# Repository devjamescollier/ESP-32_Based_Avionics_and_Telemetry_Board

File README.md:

# ESP32-Based Avionics & Telemetry Board

2S Li-Po flight computer built around an ESP32-WROOM-32E module. Fuses two IMUs, a magnetometer, and a barometer, logs flight data to microSD, and drives four servos and one ESC from a fused, reverse-polarity-protected battery input with a switched servo rail.

Designed for small fixed-wing aircraft with USB programming, multiple test points, and battery-voltage monitoring.

## Table of Contents
- [Schematic](#schematic)
- [Layout](#layout)
- [3D Model](#3d-model)
- [Overview](#overview)
- [Specifications](#specifications)
- [Results](#results)
- [Software](#software)
- [Tech Stack](#tech-stack)
- [Equipment](#equipment)
- [Manufacturing](#manufacturing)
- [Repository Structure](#repository-structure)
- [Contact](#contact)
- [License](#license)

## Schematic

## Layout

## 3D Model

## Overview

The board is a compact 4-layer flight computer centred on an ESP32-WROOM-32E module.

| Section                         | Description                                                                                                            |
| ---                             | ---                                                                                                                    |
| **Digital Core**                | The ESP32-WROOM-32E runs sensor fusion, logging, and actuator control, programmed through a CP2102N USB-UART bridge.   |
| **Sensors**                     | LSM6DSV32X and ASM330LHH IMUs on SPI, plus an LIS3MDL magnetometer and MS5611 barometer on I²C.                        |
| **Actuator Outputs**            | Four servo headers and one ESC header, each with a 1 kΩ series resistor and 100 kΩ pull-down to stay low through reset. |
| **User Interface**              | EN and BOOT buttons, three status LEDs, an active buzzer, and a microSD socket for data logging.                       |
| **Power**                       | An XT30 input feeds a 15 A fuse, P-FET reverse-battery protection, a switched servo rail, and an AP63203 3.3 V buck regulator. |

## Specifications

| Parameter                         | Value                                  |
| --------------------------------- | -------------------------------------- |
| **Microcontroller**               | ESP32-WROOM-32E-N4                     |
| **IMUs**                          | LSM6DSV32X and ASM330LHH, SPI          |
| **Magnetometer**                  | LIS3MDL, I²C                           |
| **Barometer**                     | MS5611-01BA03, I²C                     |
| **Storage**                       | microSD, SPI                           |
| **Outputs**                       | 4 servo + 1 ESC                        |
| **Power Input**                   | 2S Li-Po, 6.0–8.4 V                    |
| **Idle Current**                  | 48 mA (battery), 62 mA (USB)           |
| **Servo Rail Rating**             | 6 A continuous (calculated)            |
| **Regulation**                    | 3.301 V, 8.4 mVpp ripple               |
| **Board mass**                    | 18.4 g                                 |
| **Board size**                    | 80 mm × 50 mm                          |

## Results

PCB measurements from the JLCPCB-assembled prototype:

| Measurement           | Expected        | Measured          | Notes                            |
| --------------------: | --------------: | ----------------: | -------------------------------: |
| **VBAT**              | 7.4–8.4 V       | 8.21 V            | 2S Li-Po at ~80 % charge         |
| **SERVO_PWR**         | ≈ VBAT          | 8.19 V            | Q4 drop ≈ 20 mV                  |
| **REG_IN**            | Supply − Vf     | 7.92 V / 4.78 V   | From servo rail / USB            |
| **+3.3 V**            | 3.30 V ± 2 %    | 3.301 V           | 8.4 mVpp ripple at 1.1 MHz       |
| **V_SENSE**           | 2.30 V          | 2.31 V            | Battery-voltage ADC divider      |
| **Soft start**        | ~1 ms           | 1.1 ms            | Servo-rail switch-on             |
| **Reverse polarity**  | No conduction   | 0 mA              | −8.2 V on J7 for 5 s, no damage  |
| **IMU accel (Z)**     | +1.000 g        | +0.998 / +0.997 g | LSM6DSV32X / ASM330LHH, flat     |
| **IMU gyro**          | ~0 °/s          | < ±0.18 °/s       | Both IMUs, static                |
| **Magnetic field**    | Geomagnetic     | 28.5 / −1.2 / 41.0 µT | LIS3MDL, flat, north-aligned |
| **Pressure**          | ~1013 hPa       | 1013.2 hPa        | MS5611, 23.6 °C                  |
| **Soak temperature**  | No brown-out    | 41.2 °C           | ESP32 after 30 min, buck 38.7 °C |

USB programming, sensor IDs, I²C, microSD (SPI), and clean PWM edges (< 40 ns) on all outputs were verified using a digital multimeter, oscilloscope, bench power supply, and thermometer. Servo-rail load testing at 6 A, vibration, and EMI testing are still to be performed.

## Software

The diagnostic firmware targets the ESP32-WROOM-32E and is written in C with ESP-IDF.

### Programming

1. Install ESP-IDF (tested with v6.1-beta1).
2. Open [`Software/fc_diag`](Software/fc_diag) and run `idf.py set-target esp32`.
3. Build the firmware with `idf.py build`.
4. Connect the board over USB; the auto-program circuit enters the bootloader automatically.
5. Flash and monitor the firmware with `idf.py -p PORT flash monitor`.

## Tech Stack

| PCB Design | Firmware Development | Version Control | Repository Hosting | Language |
| :--------: | :------------------: | :-------------: | :----------------: | :------: |
|  |  |  |  |  |

## Equipment

| Tool                   | Model | Purpose                                              |
| ---------------------- | ----- | ---------------------------------------------------- |
| **Oscilloscope**       | —     | Soft-start, ripple, and PWM edge measurements        |
| **Multimeter**         | —     | Rail voltages, continuity, and current draw          |
| **Bench power supply** | —     | Current-limited power-up and reverse-polarity test   |
| **Thermometer**        | —     | Component temperatures during the soak test          |
| **Loupe (10×)**        | —     | Solder-joint and assembly inspection                 |
| **Soldering station**  | —     | Hand assembly of the through-hole components         |

## Manufacturing

Production files are provided in the [`Manufacturing`](Manufacturing/) directory:

- [`ESP-32_Based_Avionics_Telemetry_Board_Gerbers.zip`](Manufacturing/ESP-32_Based_Avionics_Telemetry_Board_Gerbers.zip) — Gerber and drill archive, ready to upload
- [`BOM.csv`](Manufacturing/Assembly/BOM.csv) — Bill of materials with LCSC part numbers (SMT parts)
- [`positions.csv`](Manufacturing/Assembly/positions.csv) — Component placement data (CPL)
- [`Hand_Assembly_THT.csv`](Manufacturing/Assembly/Hand_Assembly_THT.csv) — Through-hole parts to hand-solder
- [`CPL_rotation_review.csv`](Manufacturing/Assembly/CPL_rotation_review.csv) — Polarized parts to check in JLCPCB's placement preview
- [`Gerbers`](Manufacturing/Gerbers/) — Copper, mask, silkscreen, paste, outline, and drill files

### Ordering from JLCPCB

1. Upload the Gerber zip. Set **Layers: 4**, **Thickness: 1.6 mm**, **Stackup: JLC04161H-7628**, **Surface finish: ENIG**. Leave everything else at the default.
2. Enable **PCB Assembly**, top side only, and upload `BOM.csv` and `positions.csv`.
3. In the placement preview, check each part in `CPL_rotation_review.csv`, especially the diodes, LEDs, electrolytic capacitors, MOSFETs and ICs. Fix any rotations before confirming.
4. Hand-solder the through-hole parts in `Hand_Assembly_THT.csv` (buzzer, servo and ESC headers, XT30, slide switch). Their LCSC numbers are listed so they can be ordered from LCSC in the same order.

All 37 LCSC part numbers were in stock in the JLCPCB parts snapshot checked on 2026-11-09. Re-confirm live stock at checkout.

### Notes

- The servo rail (pin 2 of J2–J5) carries the battery voltage directly, up to 8.4 V. Use high-voltage (HV) servos rated for 2S.
- The ESC header's centre pin (J8 pin 2) is not connected, so the ESC's BEC cannot back-feed the board.

Design and manufacturing checks (ERC, DRC, BOM/CPL reconciliation, Gerber checks) are recorded in [`Docs/Verification`](Docs/Verification/VERIFICATION.md).

## Repository Structure

```text
ESP-32_Based_Avionics_and_Telemetry_Board
├── Docs                                                                           Contains board related images and verification records
│   ├── Images                                                                     Contains images of the board render, board layout, and board schematic
│   │   ├── ESP-32_Based_Avionics_Telemetry_Board_3D_Model.png                     3D model in PNG format
│   │   ├── ESP-32_Based_Avionics_Telemetry_Board_Layout.png                       Layout in PNG format
│   │   ├── ESP-32_Based_Avionics_Telemetry_Board_Schematic.png                    Schematic in PNG format
│   │   └── ESP-32_Based_Avionics_Telemetry_Board_Schematic.pdf                    Schematic in PDF format
│   └── Verification                                                               Contains ERC, DRC, BOM, and Gerber check records
│       ├── BOM_CPL_Check.json                                                     BOM and placement reconciliation
│       ├── DRC.rpt                                                                DRC report
│       ├── ERC.rpt                                                                ERC report
│       ├── Gerber_Check.txt                                                       Gerber and drill check
│       └── VERIFICATION.md                                                        Design-check summary
├── Hardware                                                                       Contains all KiCad PCB files
│   └── KiCad_Files                                                                Contains 3D models for board render, footprints for layout, KiCad project files, and symbols for schematic.
│       ├── 3D_Models                                                              Contains STEP files for the 3D render of the board
│       │   ├── Buzzer_12x9.5RM7.6.step                                            STEP for buzzer
│       │   ├── C_0603_1608Metric.step                                             STEP for 0603 capacitors
│       │   ├── C_0805_2012Metric.step                                             STEP for 0805 capacitors
│       │   ├── CP_Elec_6.3x5.4.step                                               STEP for electrolytic capacitors
│       │   ├── D_SMA.step                                                         STEP for SS54 diodes
│       │   ├── D_SOD-323.step                                                     STEP for B5819WS diode
│       │   ├── ESP32-WROOM-32E.step                                               STEP for ESP32-WROOM-32E module
│       │   ├── L_Changjiang_FNR4030S.step                                         STEP for buck inductor
│       │   ├── LED_0603_1608Metric.step                                           STEP for LEDs
│       │   ├── LGA-12_2x2mm_P0.5mm.step                                           STEP for LIS3MDL magnetometer
│       │   ├── LGA-14_3x2.5mm_P0.5mm_LayoutBorder3x4y.step                        STEP for IMUs
│       │   ├── Littelfuse_0451.step                                               STEP for 15 A fuse
│       │   ├── microSD_HC_Hirose_DM3AT-SF-PEJM5.step                              STEP for microSD socket
│       │   ├── Molex_105017-0001.step                                             STEP for USB Micro-B receptacle
│       │   ├── PinHeader_1x03_P2.54mm_Vertical.step                               STEP for servo and ESC headers
│       │   ├── QFN-28-1EP_5x5mm_P0.5mm_EP3.35x3.35mm.step                         STEP for CP2102N
│       │   ├── R_0603_1608Metric.step                                             STEP for 0603 resistors
│       │   ├── SOIC-8_3.9x4.9mm_P1.27mm.step                                      STEP for AO4407A MOSFETs
│       │   ├── SOT-23-6.step                                                      STEP for USBLC6-2SC6
│       │   ├── SOT-23.step                                                        STEP for MMBT3904 transistors
│       │   ├── SS12D10G5.step                                                     STEP for slide switch
│       │   ├── TS-1187A-B-A-B.step                                                STEP for tactile switches
│       │   ├── TSOT-23-6.step                                                     STEP for AP63203 buck regulator
│       │   └── XT30PW-M.step                                                      STEP for XT30 battery connector
│       ├── Footprints                                                             Contains footprints for PCB components
│       │   └── Avionics_Footprints.pretty                                         Contains custom board footprints
│       │       ├── ESP32-WROOM-32E_Espressif.kicad_mod
│       │       ├── SW_Slide_SPDT_Vertical_ShouHan_SS12D10_P4.8mm.kicad_mod
│       │       ├── TE_MS5611-01BA03_LGA-8_3x5mm_P1.25mm.kicad_mod
│       │       └── USB_Micro-B_Molex-105017-0001_EdgeSilk.kicad_mod
│       ├── ESP-32_Based_Avionics_Telemetry_Board.kicad_pcb                        KiCad PCB file
│       ├── ESP-32_Based_Avionics_Telemetry_Board.kicad_pro                        KiCad project file
│       ├── ESP-32_Based_Avionics_Telemetry_Board.kicad_sch                        KiCad Schematic file
│       ├── fp-lib-table
│       ├── sym-lib-table
│       └── Symbols                                                                Contains schematic symbols for PCB schematic
│           └── FC_Fixed.kicad_sym                                                 ESP32, CP2102N, sensor, and MS5611 symbols
├── LICENSE                                                                        CERN Open Hardware Licence Version 2 - Permissive for hardware
├── Manufacturing                                                                  Contains bill of materials, pick-and-place, and Gerber files.
│   ├── Assembly                                                                   Contains bill of materials and pick-and-place
│   │   ├── BOM.csv                                                                Bill of materials
│   │   ├── CPL_rotation_review.csv                                                Polarized parts placement review
│   │   ├── Hand_Assembly_THT.csv                                                  Through-hole parts for hand soldering
│   │   └── positions.csv                                                          Pick-and-place
│   ├── Gerbers                                                                    Contains Gerber files
│   │   ├── ESP-32_Based_Avionics_Telemetry_Board-B_Cu.gbl
│   │   ├── ESP-32_Based_Avionics_Telemetry_Board-B_Mask.gbs
│   │   ├── ESP-32_Based_Avionics_Telemetry_Board-B_Paste.gbp
│   │   ├── ESP-32_Based_Avionics_Telemetry_Board-B_Silkscreen.gbo
│   │   ├── ESP-32_Based_Avionics_Telemetry_Board-Edge_Cuts.gm1
│   │   ├── ESP-32_Based_Avionics_Telemetry_Board-F_Cu.gtl
│   │   ├── ESP-32_Based_Avionics_Telemetry_Board-F_Mask.gts
│   │   ├── ESP-32_Based_Avionics_Telemetry_Board-F_Paste.gtp
│   │   ├── ESP-32_Based_Avionics_Telemetry_Board-F_Silkscreen.gto
│   │   ├── ESP-32_Based_Avionics_Telemetry_Board-GND.g1
│   │   ├── ESP-32_Based_Avionics_Telemetry_Board-job.gbrjob
│   │   ├── ESP-32_Based_Avionics_Telemetry_Board-NPTH-drl_map.gbr
│   │   ├── ESP-32_Based_Avionics_Telemetry_Board-NPTH.drl
│   │   ├── ESP-32_Based_Avionics_Telemetry_Board-PTH-drl_map.gbr
│   │   ├── ESP-32_Based_Avionics_Telemetry_Board-PTH.drl
│   │   └── ESP-32_Based_Avionics_Telemetry_Board-PWR.g2
│   └── ESP-32_Based_Avionics_Telemetry_Board_Gerbers.zip                          Gerber archive for JLCPCB upload
├── Software                                                                       Contains C firmware and software license
│   ├── LICENSE                                                                    MIT License for firmware
│   └── fc_diag                                                                    ESP-IDF diagnostic firmware project
│       ├── CMakeLists.txt
│       ├── sdkconfig.defaults
│       └── main
│           ├── CMakeLists.txt
│           └── fc_diag.c                                                          Firmware for ESP32
└── README.md                                                                      Project README
```

## Contact
- GitHub: [@devjamescollier](https://github.com/devjamescollier)
- Email: [jwcollie@usc.edu](mailto:jwcollie@usc.edu)

## License

Copyright © 2026 James Collier

The hardware design files are licensed under the CERN Open Hardware
Licence Version 2 – Permissive. See [LICENSE](LICENSE).

The firmware is licensed under the MIT License. See
[Software/LICENSE](Software/LICENSE).

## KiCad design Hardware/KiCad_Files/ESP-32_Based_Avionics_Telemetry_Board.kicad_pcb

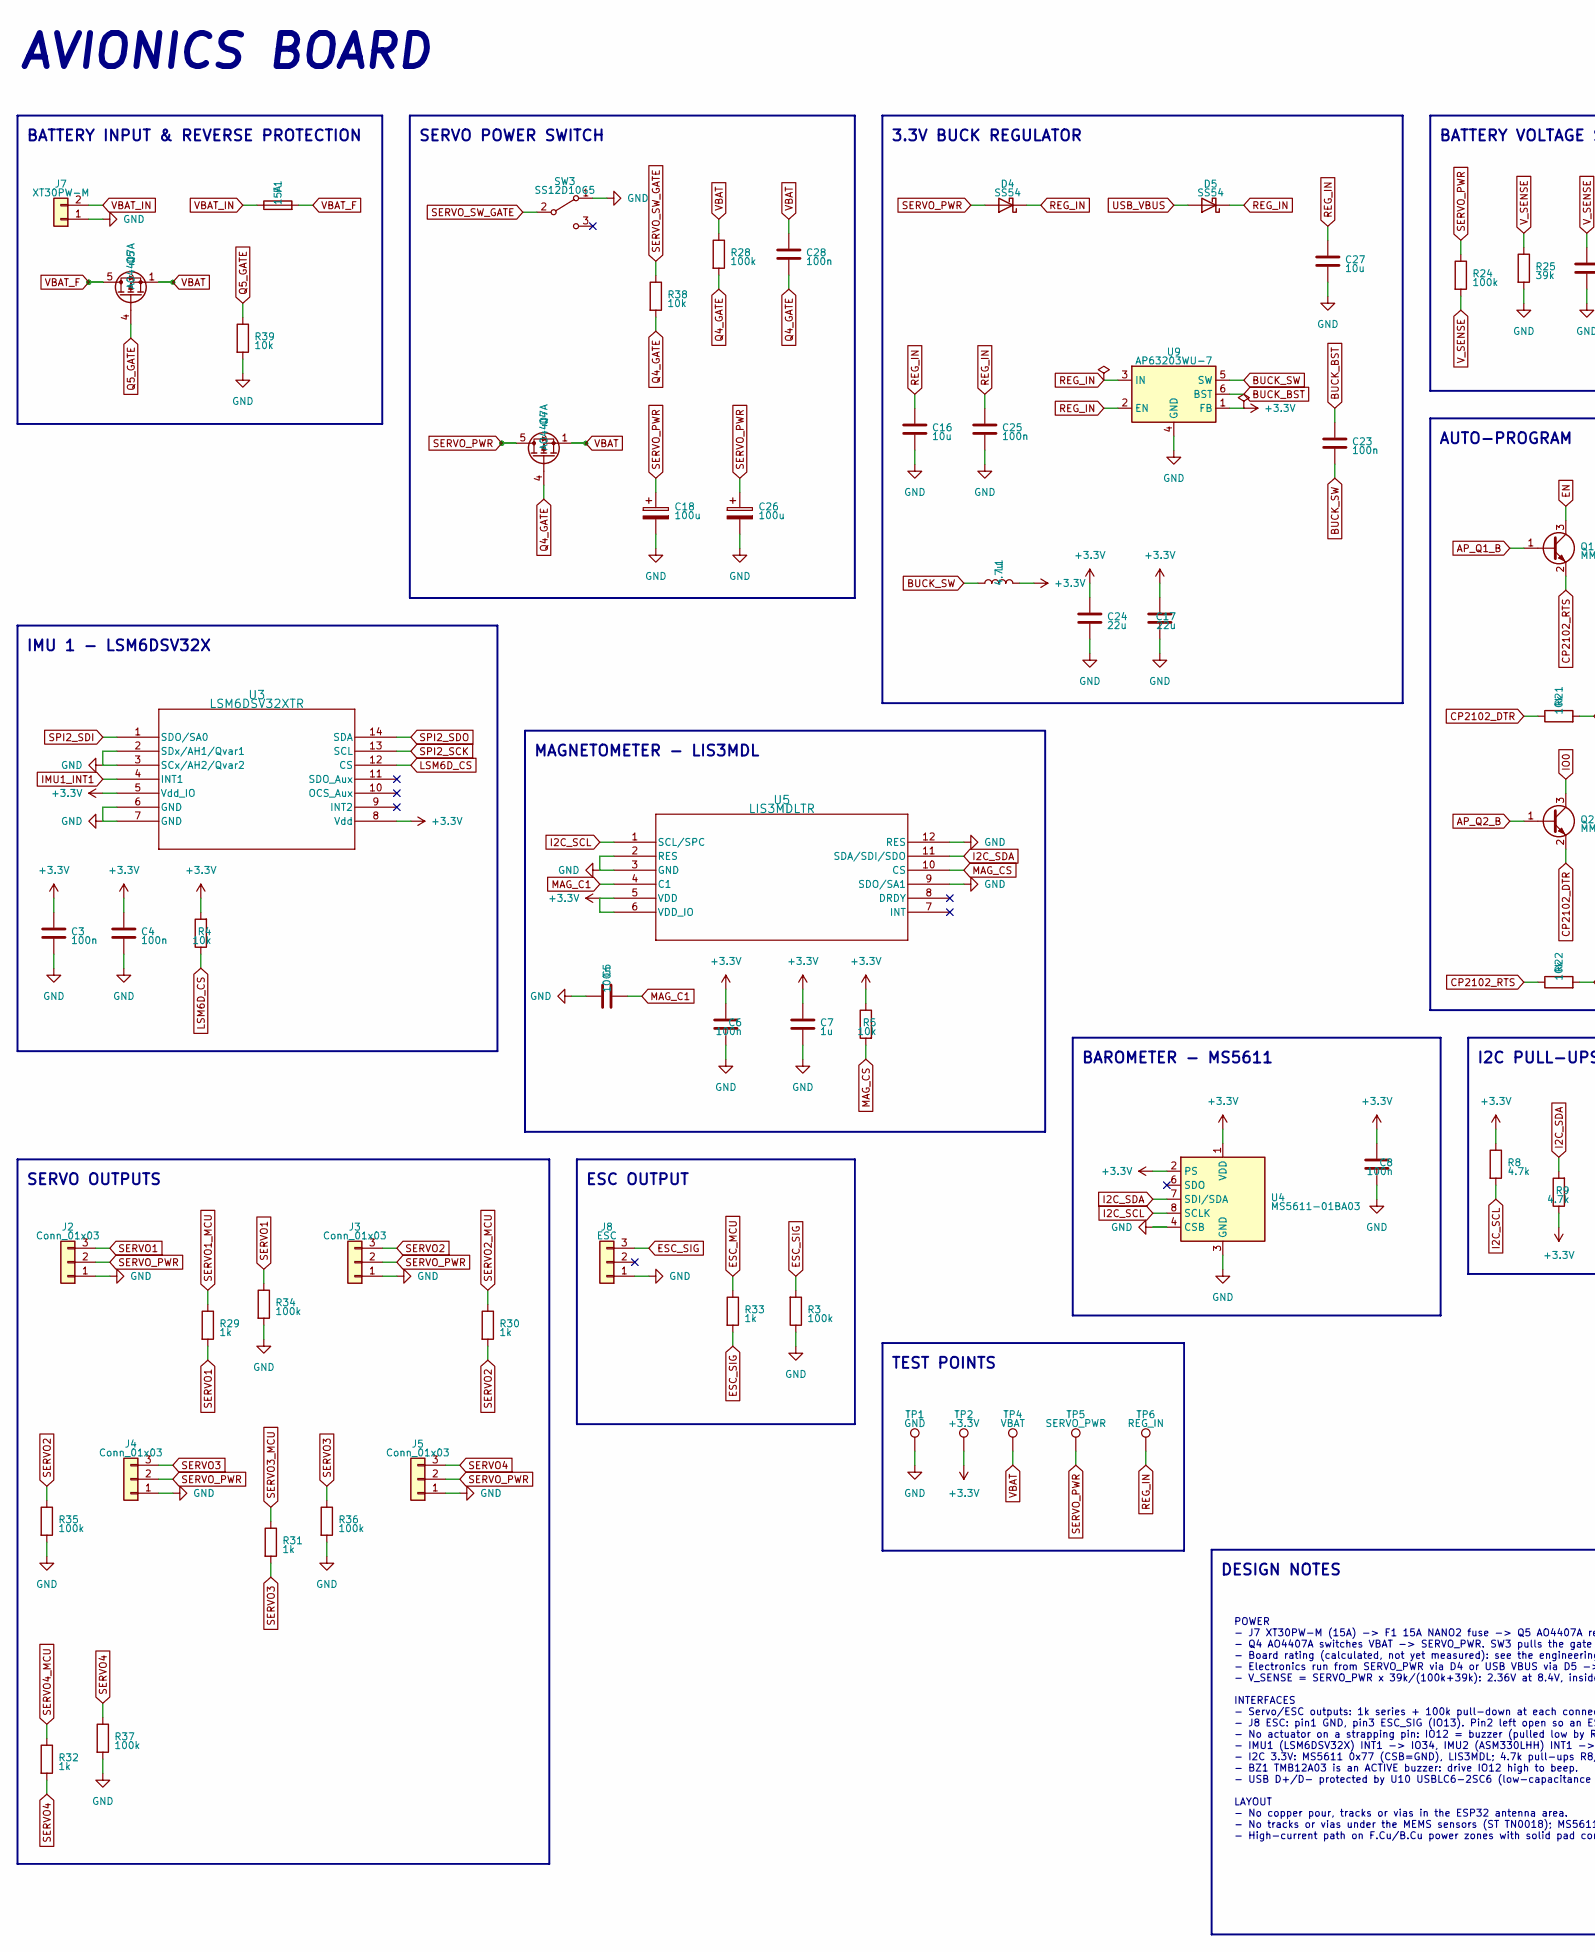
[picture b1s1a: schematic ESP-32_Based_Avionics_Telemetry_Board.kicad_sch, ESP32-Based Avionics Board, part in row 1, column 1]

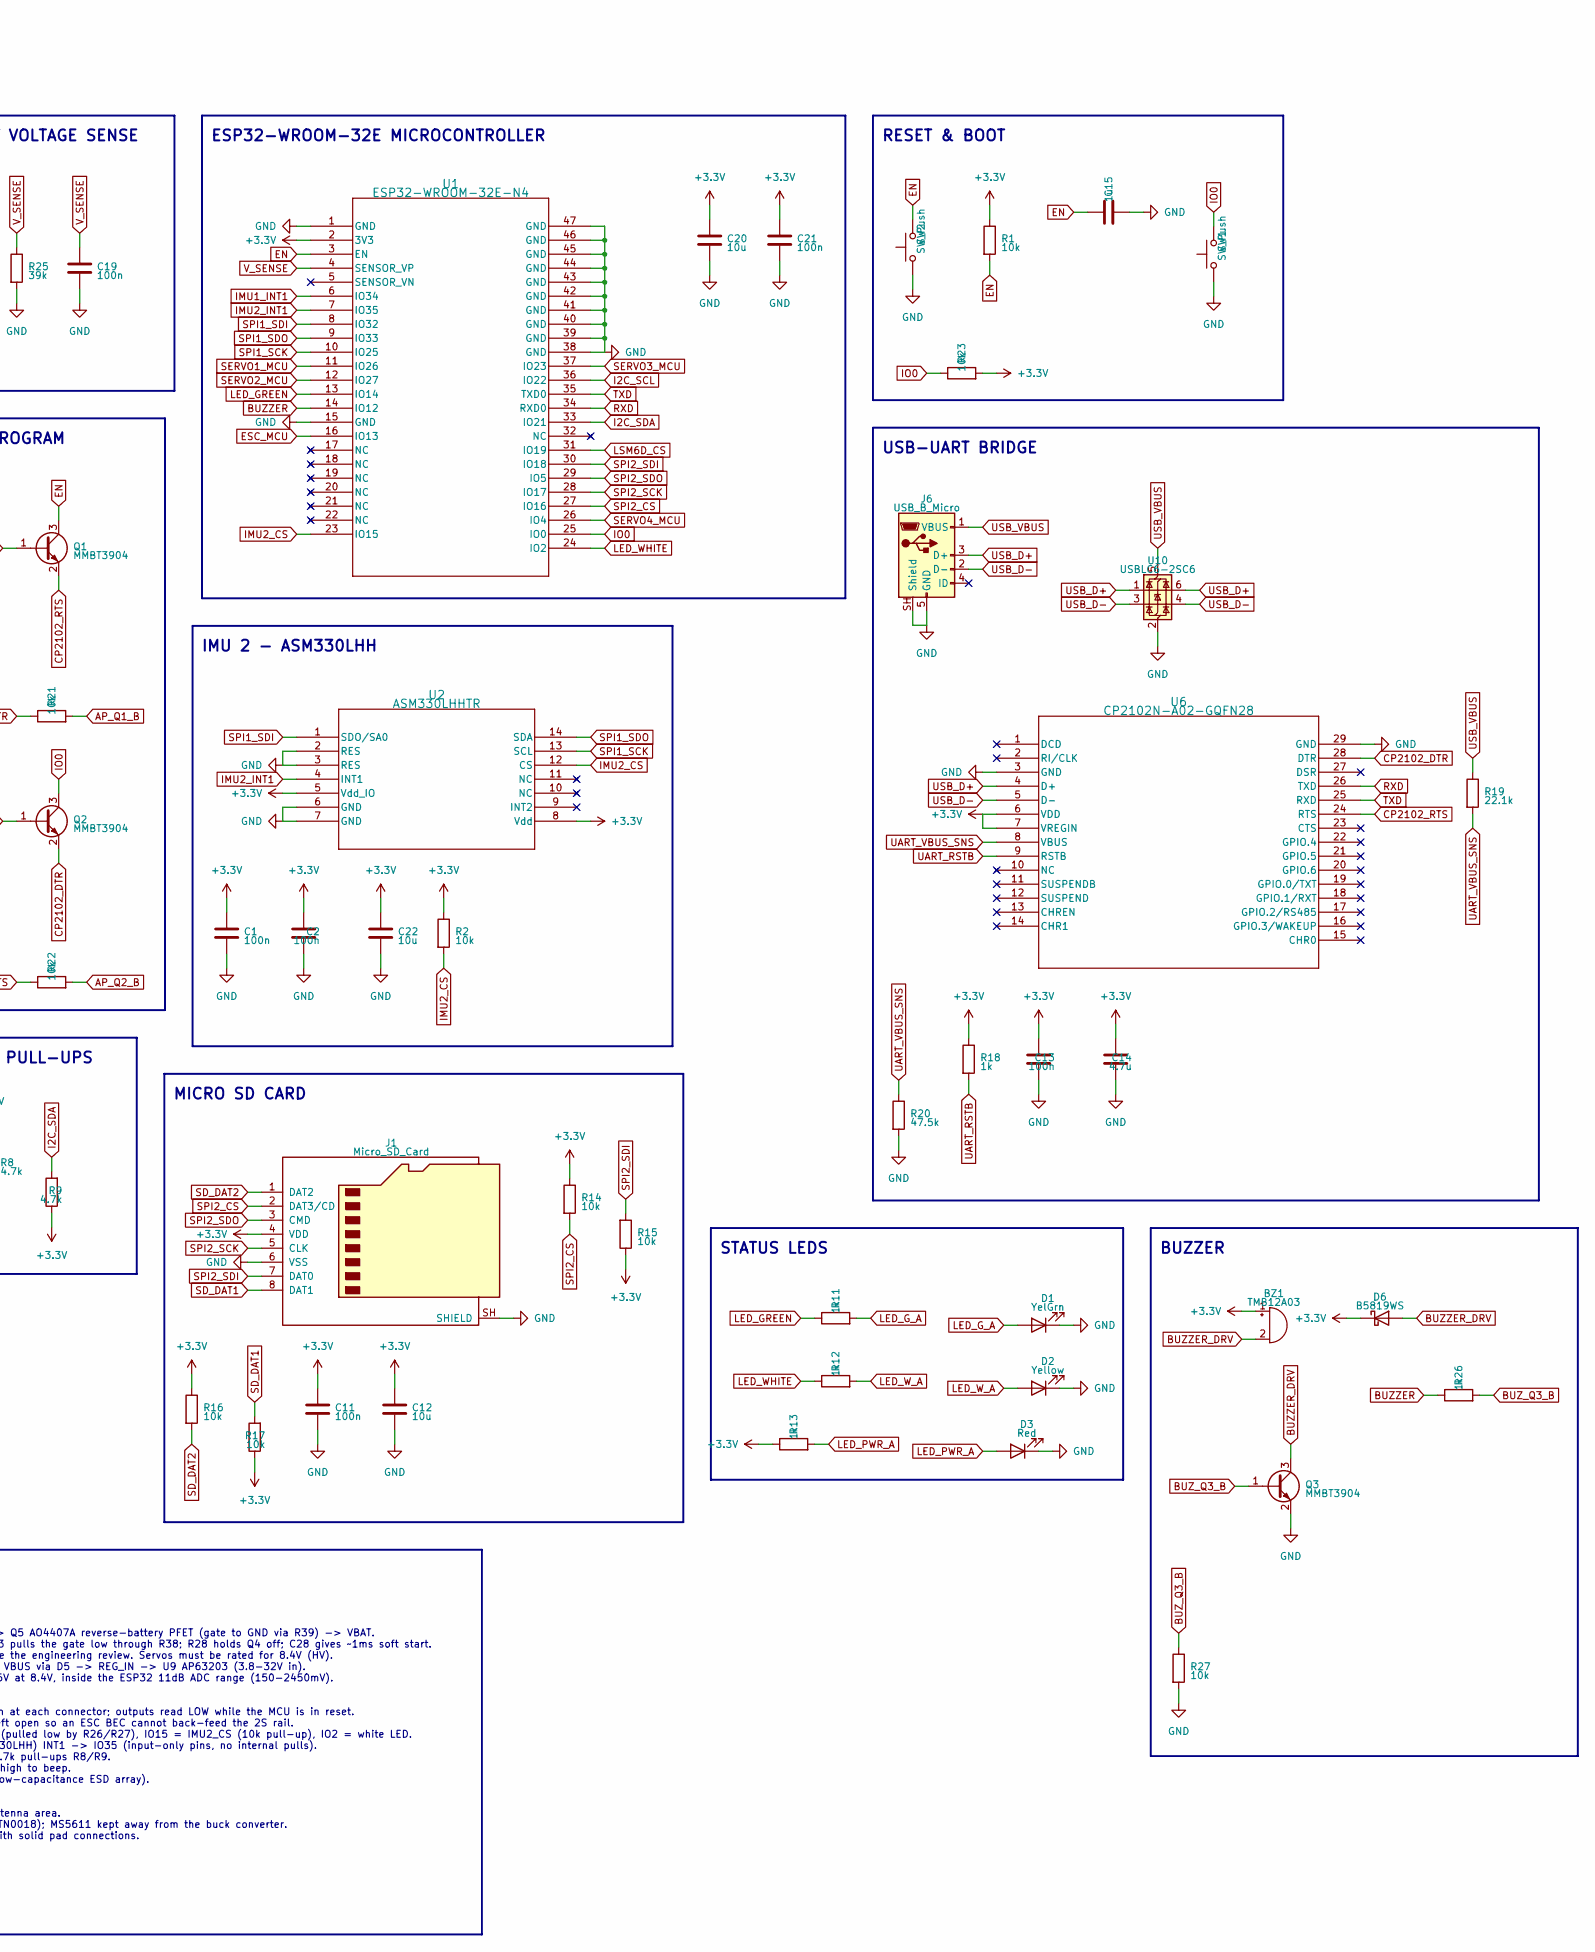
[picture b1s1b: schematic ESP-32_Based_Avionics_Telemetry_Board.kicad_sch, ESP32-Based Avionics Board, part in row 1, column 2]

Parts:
BZ1: TMB12A03; Buzzer_12x9.5RM7.6; LCSC C96222
C1, C2, C3, C4, C5, C6, C8, C11, C13, C19, C21, C23, C25, C28: 100n; C_0603_1608Metric; LCSC C14663
C7, C15: 1u; C_0603_1608Metric; LCSC C15849
C12, C16, C20, C22, C27: 10u; C_0805_2012Metric; LCSC C15850
C14: 4.7u; C_0805_2012Metric; LCSC C1779
C17, C24: 22u; C_0805_2012Metric; LCSC C45783
C18, C26: 100u; CP_Elec_6.3x5.4; LCSC C7469933
D1: YelGrn; LED_0603_1608Metric; LCSC C965805
D2: Yellow; LED_0603_1608Metric; LCSC C89811
D3: Red; LED_0603_1608Metric; LCSC C2286
D4, D5: SS54; D_SMA; LCSC C22452
D6: B5819WS; D_SOD-323; LCSC C64886
F1: 15A; Fuse_Littelfuse-NANO2-451_453; LCSC C44480
J1: Micro_SD_Card; microSD_HC_Hirose_DM3AT-SF-PEJM5; LCSC C114218
J2, J3, J4, J5: Conn_01x03; PinHeader_1x03_P2.54mm_Vertical; LCSC C49257
J6: USB_B_Micro; USB_Micro-B_Molex-105017-0001_EdgeSilk; LCSC C136000
J7: XT30PW-M; AMASS_XT30PW-M_1x02_P2.50mm_Horizontal; LCSC C431092
J8: ESC; PinHeader_1x03_P2.54mm_Vertical; LCSC C49257
L1: 4.7u; L_Changjiang_FNR4030S; MPN FNR4030S4R7MT; LCSC C167874
Q1, Q2, Q3: MMBT3904; SOT-23; LCSC C20526
Q4, Q5: AO4407A; SOIC-8_3.9x4.9mm_P1.27mm; LCSC C16072
R1, R2, R4, R5, R14, R15, R16, R17, R21, R22, R23, R27, R38, R39: 10k; R_0603_1608Metric; LCSC C25804
R3, R24, R28, R34, R35, R36, R37: 100k; R_0603_1608Metric; LCSC C25803
R8, R9: 4.7k; R_0603_1608Metric; LCSC C23162
R11, R12, R13, R18, R26, R29, R30, R31, R32, R33: 1k; R_0603_1608Metric; LCSC C21190
R19: 22.1k; R_0603_1608Metric; LCSC C137768
R20: 47.5k; R_0603_1608Metric; LCSC C23061
R25: 39k; R_0603_1608Metric; LCSC C23153
SW1, SW2: SW_Push; SW_Push_1P1T_XKB_TS-1187A; LCSC C318884
SW3: SS12D10G5; SW_Slide_SPDT_Vertical_ShouHan_SS12D10_P4.8mm; LCSC C7431054
TP1: GND; TestPoint_Pad_D1.5mm
TP2: +3.3V; TestPoint_Pad_D1.5mm
TP4: VBAT; TestPoint_Pad_D1.5mm
TP5: SERVO_PWR; TestPoint_Pad_D1.5mm
TP6: REG_IN; TestPoint_Pad_D1.5mm
U1: ESP32-WROOM-32E-N4; ESP32-WROOM-32E_Espressif; LCSC C701341
U2: ASM330LHHTR; LGA-14_3x2.5mm_P0.5mm_LayoutBorder3x4y; LCSC C459826
U3: LSM6DSV32XTR; LGA-14_3x2.5mm_P0.5mm_LayoutBorder3x4y; LCSC C22461202
U4: MS5611-01BA03; TE_MS5611-01BA03_LGA-8_3x5mm_P1.25mm; LCSC C15639
U5: LIS3MDLTR; LGA-12_2x2mm_P0.5mm; LCSC C478483
U6: CP2102N-A02-GQFN28; QFN-28-1EP_5x5mm_P0.5mm_EP3.35x3.35mm; LCSC C964632
U9: AP63203WU-7; TSOT-23-6; LCSC C780769
U10: USBLC6-2SC6; SOT-23-6; LCSC C7519

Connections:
+3.3V: BZ1.1 (+), C1.2, C2.2, C3.2, C4.2, C6.1, C7.1, C8.2, C11.1, C12.1, C13.2, C14.2, C17.1, C20.1, C21.1, C22.1, C24.1, D6.1 (K), J1.4 (VDD), L1.2, R1.1, R2.1, R4.2, R5.1, R8.1, R9.1, R13.1, R14.1, R15.1, R16.1, R17.1, R18.1, R23.2, TP2.1, U1.2 (3V3), U2.5 (Vdd_IO), U2.8 (Vdd), U3.5 (Vdd_IO), U3.8 (Vdd), U4.1 (VDD), U4.2 (PS), U5.5 (VDD), U5.6 (VDD_IO), U6.6 (VDD), U6.7 (VREGIN), U9.1 (FB)
AP_Q1_B: Q1.1 (B), R21.2
AP_Q2_B: Q2.1 (B), R22.2
BUCK_BST: C23.1, U9.6 (BST)
BUCK_SW: C23.2, L1.1, U9.5 (SW)
BUZZER: R26.1, U1.14 (IO12)
BUZZER_DRV: BZ1.2 (-), D6.2 (A), Q3.3 (C)
BUZ_Q3_B: Q3.1 (B), R26.2, R27.1
CP2102_DTR: Q2.2 (E), R21.1, U6.28 (DTR)
CP2102_RTS: Q1.2 (E), R22.1, U6.24 (RTS)
EN: C15.1, Q1.3 (C), R1.2, SW2.2, U1.3 (EN)
ESC_MCU: R33.1, U1.16 (IO13)
ESC_SIG: J8.3, R3.2, R33.2
GND: C1.1, C2.1, C3.1, C4.1, C5.2, C6.2, C7.2, C8.1, C11.2, C12.2, C13.1, C14.1, C15.2, C16.2, C17.2, C18.2, C19.2, C20.2, C21.2, C22.2, C24.2, C25.2, C26.2, C27.2, D1.1 (K), D2.1 (K), D3.1 (K), J1.6 (VSS), J1.SH (SHIELD), J2.1, J3.1, J4.1, J5.1, J6.5 (GND), J6.SH (Shield), J7.1, J8.1, Q3.2 (E), R3.1, R20.2, R25.2, R27.2, R34.2, R35.2, R36.2, R37.2, R39.2, SW1.1, SW2.1, SW3.1 (A), TP1.1, U1.1 (GND), U1.15 (GND), U1.38 (GND), U1.39 (GND), U1.40 (GND), U1.41 (GND), U1.42 (GND), U1.43 (GND), U1.44 (GND), U1.45 (GND), U1.46 (GND), U1.47 (GND), U2.2 (RES), U2.3 (RES), U2.6 (GND), U2.7 (GND), U3.2 (SDx/AH1/Qvar1), U3.3 (SCx/AH2/Qvar2), U3.6 (GND), U3.7 (GND), U4.3 (GND), U4.4 (CSB), U4.5 (CSB), U5.2 (RES), U5.3 (GND), U5.9 (SDO/SA1), U5.12 (RES), U6.3 (GND), U6.29 (GND), U9.4 (GND), U10.2 (GND)
I2C_SCL: R8.2, U1.36 (IO22), U4.8 (SCLK), U5.1 (SCL/SPC)
I2C_SDA: R9.2, U1.33 (IO21), U4.7 (SDI/SDA), U5.11 (SDA/SDI/SDO)
IMU1_INT1: U1.6 (IO34), U3.4 (INT1)
IMU2_CS: R2.2, U1.23 (IO15), U2.12 (CS)
IMU2_INT1: U1.7 (IO35), U2.4 (INT1)
IO0: Q2.3 (C), R23.1, SW1.2, U1.25 (IO0)
LED_GREEN: R11.1, U1.13 (IO14)
LED_G_A: D1.2 (A), R11.2
LED_PWR_A: D3.2 (A), R13.2
LED_WHITE: R12.1, U1.24 (IO2)
LED_W_A: D2.2 (A), R12.2
LSM6D_CS: R4.1, U1.31 (IO19), U3.12 (CS)
MAG_C1: C5.1, U5.4 (C1)
MAG_CS: R5.2, U5.10 (CS)
Q4_GATE: C28.2, Q4.4 (G), R28.2, R38.2
Q5_GATE: Q5.4 (G), R39.1
REG_IN: C16.1, C25.1, C27.1, D4.1 (K), D5.1 (K), TP6.1, U9.2 (EN), U9.3 (IN)
RXD: U1.34 (RXD0), U6.26 (TXD)
SD_DAT1: J1.8 (DAT1), R17.2
SD_DAT2: J1.1 (DAT2), R16.2
SERVO1: J2.3, R29.2, R34.1
SERVO1_MCU: R29.1, U1.11 (IO26)
SERVO2: J3.3, R30.2, R35.1
SERVO2_MCU: R30.1, U1.12 (IO27)
SERVO3: J4.3, R31.2, R36.1
SERVO3_MCU: R31.1, U1.37 (IO23)
SERVO4: J5.3, R32.2, R37.1
SERVO4_MCU: R32.1, U1.26 (IO4)
SERVO_PWR: C18.1, C26.1, D4.2 (A), J2.2, J3.2, J4.2, J5.2, Q4.5 (D), Q4.6 (D), Q4.7 (D), Q4.8 (D), R24.1, TP5.1
SERVO_SW_GATE: R38.1, SW3.2 (B)
SPI1_SCK: U1.10 (IO25), U2.13 (SCL)
SPI1_SDI: U1.8 (IO32), U2.1 (SDO/SA0)
SPI1_SDO: U1.9 (IO33), U2.14 (SDA)
SPI2_CS: J1.2 (DAT3/CD), R14.2, U1.27 (IO16)
SPI2_SCK: J1.5 (CLK), U1.28 (IO17), U3.13 (SCL)
SPI2_SDI: J1.7 (DAT0), R15.2, U1.30 (IO18), U3.1 (SDO/SA0)
SPI2_SDO: J1.3 (CMD), U1.29 (IO5), U3.14 (SDA)
TXD: U1.35 (TXD0), U6.25 (RXD)
UART_RSTB: R18.2, U6.9 (RSTB)
UART_VBUS_SNS: R19.2, R20.1, U6.8 (VBUS)
USB_D+: J6.3 (D+), U6.4 (D+), U10.1 (I/O1), U10.6 (I/O1)
USB_D-: J6.2 (D-), U6.5 (D-), U10.3 (I/O2), U10.4 (I/O2)
USB_VBUS: D5.2 (A), J6.1 (VBUS), R19.1, U10.5 (VBUS)
VBAT: C28.1, Q4.1 (S), Q4.2 (S), Q4.3 (S), Q5.1 (S), Q5.2 (S), Q5.3 (S), R28.1, TP4.1
VBAT_F: F1.2, Q5.5 (D), Q5.6 (D), Q5.7 (D), Q5.8 (D)
VBAT_IN: F1.1, J7.2
V_SENSE: C19.1, R24.2, R25.1, U1.4 (SENSOR_VP)

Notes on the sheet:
BATTERY INPUT & REVERSE PROTECTION
SERVO POWER SWITCH
3.3V BUCK REGULATOR
BATTERY VOLTAGE SENSE
ESP32-WROOM-32E MICROCONTROLLER
RESET & BOOT
USB-UART BRIDGE
AUTO-PROGRAM
IMU 1 - LSM6DSV32X
IMU 2 - ASM330LHH
MAGNETOMETER - LIS3MDL
BAROMETER - MS5611
I2C PULL-UPS
MICRO SD CARD
SERVO OUTPUTS
ESC OUTPUT
STATUS LEDS
BUZZER
TEST POINTS
DESIGN NOTES
POWER - J7 XT30PW-M (15A) -> F1 15A NANO2 fuse -> Q5 AO4407A reverse-battery PFET (gate to GND via R39) -> VBAT. - Q4 AO4407A switches VBAT -> SERVO_PWR. SW3 pulls the gate low through R38; R28 holds Q4 off; C28 gives ~1ms soft start. - Board rating (calculated, not yet measured): see the engineeri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
AVIONICS BOARD

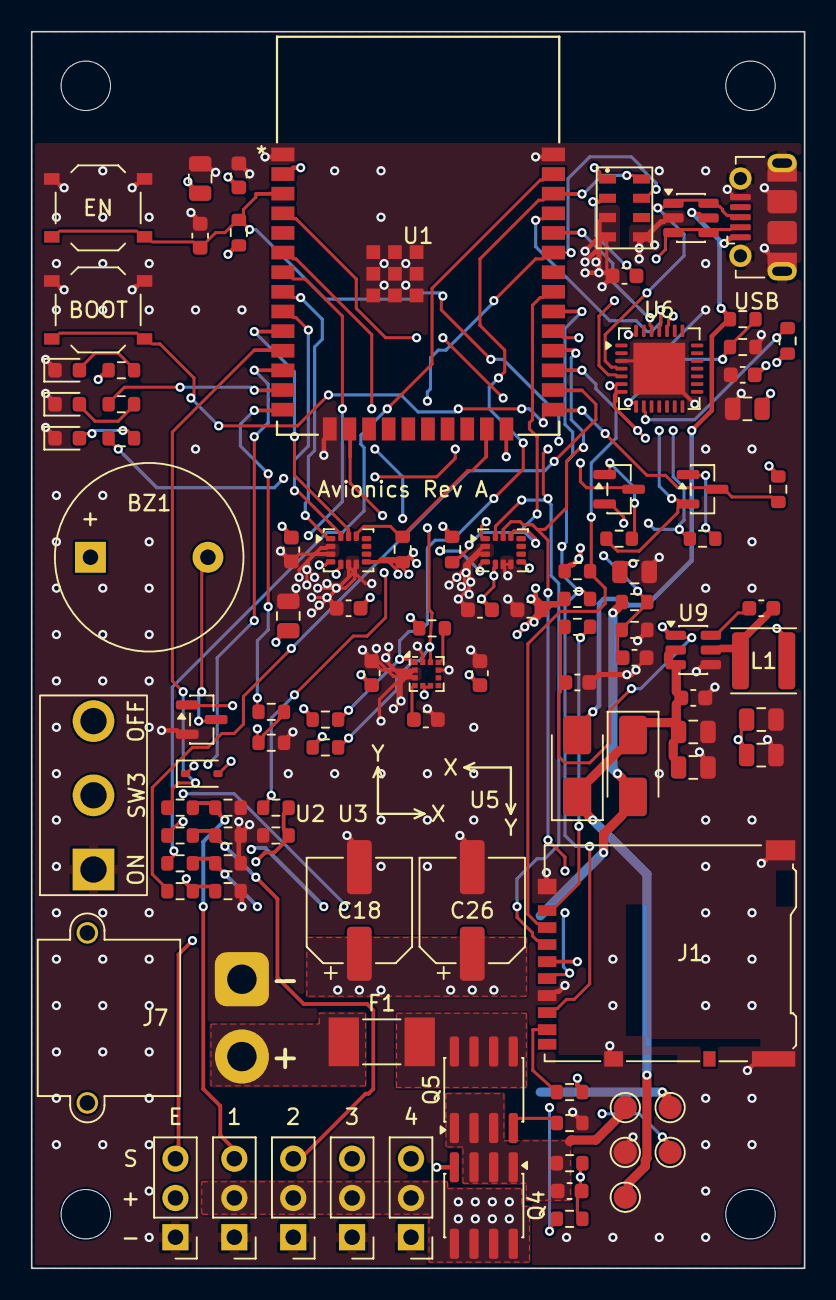
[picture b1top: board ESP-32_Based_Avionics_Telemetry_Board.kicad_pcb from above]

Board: 4 copper layers, 50.0 x 80.0 mm, 104 parts (0 on the bottom side), 61 nets.

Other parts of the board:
H1, H2, H3, H4: M3; MountingHole_3.2mm_M3

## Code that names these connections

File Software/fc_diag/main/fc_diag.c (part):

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#include "esp_chip_info.h"

/* pin map: ESP32-Based Avionics Board Rev A schematic */
#define PIN_SERVO1   GPIO_NUM_26
#define PIN_SERVO2   GPIO_NUM_27
#define PIN_SERVO3   GPIO_NUM_23
#define PIN_SERVO4   GPIO_NUM_4
#define PIN_ESC      GPIO_NUM_13
#define PIN_BUZZER   GPIO_NUM_12
#define PIN_LED_G    GPIO_NUM_14
#define PIN_LED_W    GPIO_NUM_2
#define PIN_SDA      GPIO_NUM_21
#define PIN_SCL      GPIO_NUM_22
#define SPI1_SCK     GPIO_NUM_25   /* IMU2 ASM330LHH */
#define SPI1_MISO    GPIO_NUM_32
#define SPI1_MOSI    GPIO_NUM_33
#define IMU2_CS      GPIO_NUM_15
#define SPI2_SCK     GPIO_NUM_17   /* microSD + IMU1 LSM6DSV32X */
#define SPI2_MISO    GPIO_NUM_18
#define SPI2_MOSI    GPIO_NUM_5
#define SD_CS        GPIO_NUM_16
#define IMU1_CS      GPIO_NUM_19
#define IMU1_INT1    GPIO_NUM_34
#define IMU2_INT1    GPIO_NUM_35
#define VSENSE_CH    ADC_CHANNEL_0  /* IO36 */
#define VSENSE_RATIO ((100.0f + 39.0f) / 39.0f)

static const gpio_num_t ACTUATORS[] = {PIN_SERVO1, PIN_SERVO2, PIN_SERVO3, PIN_SERVO4, PIN_ESC, PIN_BUZZER};
static const gpio_num_t SERVOS[] = {PIN_SERVO1, PIN_SERVO2, PIN_SERVO3, PIN_SERVO4};
static spi_device_handle_t imu1, imu2;
static i2c_master_bus_handle_t i2c;

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    uint8_t w2 = spi_reg(imu2, 0x0F), w1 = spi_reg(imu1, 0x0F);
    printf("IMU2 ASM330LHH  (SPI1, CS IO15) WHO_AM_I=0x%02X %s\n", w2, w2 == 0x6B ? "PASS" : "FAIL, expect 0x6B");
    printf("IMU1 LSM6DSV32X (SPI2, CS IO19) WHO_AM_I=0x%02X %s\n", w1, w1 == 0x70 ? "PASS" : "FAIL, expect 0x70");
    printf("INT1 levels: IMU1 IO34=%d IMU2 IO35=%d\n", gpio_get_level(IMU1_INT1), gpio_get_level(IMU2_INT1));
}

static void test_sd(void)
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    t.tx_data[0] = 0x03; t.tx_data[1] = 0x01;
    spi_device_polling_transmit(imu1, &t);

    gpio_set_direction(IMU1_INT1, GPIO_MODE_INPUT);
    gpio_set_direction(IMU2_INT1, GPIO_MODE_INPUT);
    report();
    for (;;) {
        uint8_t c;
        if (uart_read_bytes(UART_NUM_0, &c, 1, pdMS_TO_TICKS(1000)) <= 0) continue;
        switch (c) {
        case 'r': report(); break;
        case 'b': gpio_set_level(PIN_BUZZER, 1); vTaskDelay(pdMS_TO_TICKS(200)); gpio_set_level(PIN_BUZZER, 0); printf("beep\n"); break;
        case 'l':
            gpio_set_level(PIN_LED_G, 1); vTaskDelay(pdMS_TO_TICKS(500)); gpio_set_level(PIN_LED_G, 0);
            gpio_set_level(PIN_LED_W, 1); vTaskDelay(pdMS_TO_TICKS(500)); gpio_set_level(PIN_LED_W, 0);
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
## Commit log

2025-08-02 Add project licenses
2025-08-03 Add custom symbol library and library tables
2025-08-04 Add ESP32 and peripheral footprints
2025-08-05 Add ESP32 and sensor 3D models
2025-08-06 Add power and passive component 3D models
2025-08-08 Add avionics schematic
2025-08-11 Add four-layer PCB layout and project file
2025-08-12 Set up ESP-IDF diagnostics project
2025-08-14 Add peripheral diagnostic firmware
2025-08-15 Add ERC report
2025-08-16 Add DRC report
2025-08-17 Add four-layer Gerber and drill files
2025-08-18 Add fabrication archive and Gerber check
2025-08-19 Add BOM and placement files
2025-08-20 Add rotation review and THT assembly list
2025-08-21 Add schematic exports
2025-08-22 Add layout and 3D renders
2025-08-23 Add verification summary
2025-08-25 Add README

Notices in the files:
README.md:
Hardware License: CERN-OHL-P-2.0
Firmware License: MIT
